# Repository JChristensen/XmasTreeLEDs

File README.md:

# Xmas Tree LEDs
https://github.com/JChristensen/XmasTreeLEDs  
README file  
Jack Christensen  
Nov-2023

## License
  
Xmas Tree LEDs by Jack Christensen is licensed under a [Creative Commons Attribution-ShareAlike 4.0 International License](http://creativecommons.org/licenses/by-sa/4.0/).

## Overview
Blinkenlights for a small ceramic Christmas Tree. Uses an ATTiny84A microcontroller and a boost regulator to maintain constant voltage to the circuit. Battery is two AAA cells and fits under the base.

See the [firmware here](https://github.com/JChristensen/XmasTree).  
PC boards can be ordered from [OSH Park](https://oshpark.com/shared_projects/T9Cb02lh).  
A bill of materials is available at [Mouser Electronics](https://www.mouser.com/ProjectManager/ProjectDetail.aspx?AccessID=e903af6094) and also in this repo.  

https://github.com/JChristensen/XmasTreeLEDs/assets/762571/b531e305-ae8b-4c04-a3d2-77f9e12bad94

https://github.com/JChristensen/XmasTreeLEDs/assets/762571/8232f8c4-e6b6-4896-a1eb-c29be3a8e65b

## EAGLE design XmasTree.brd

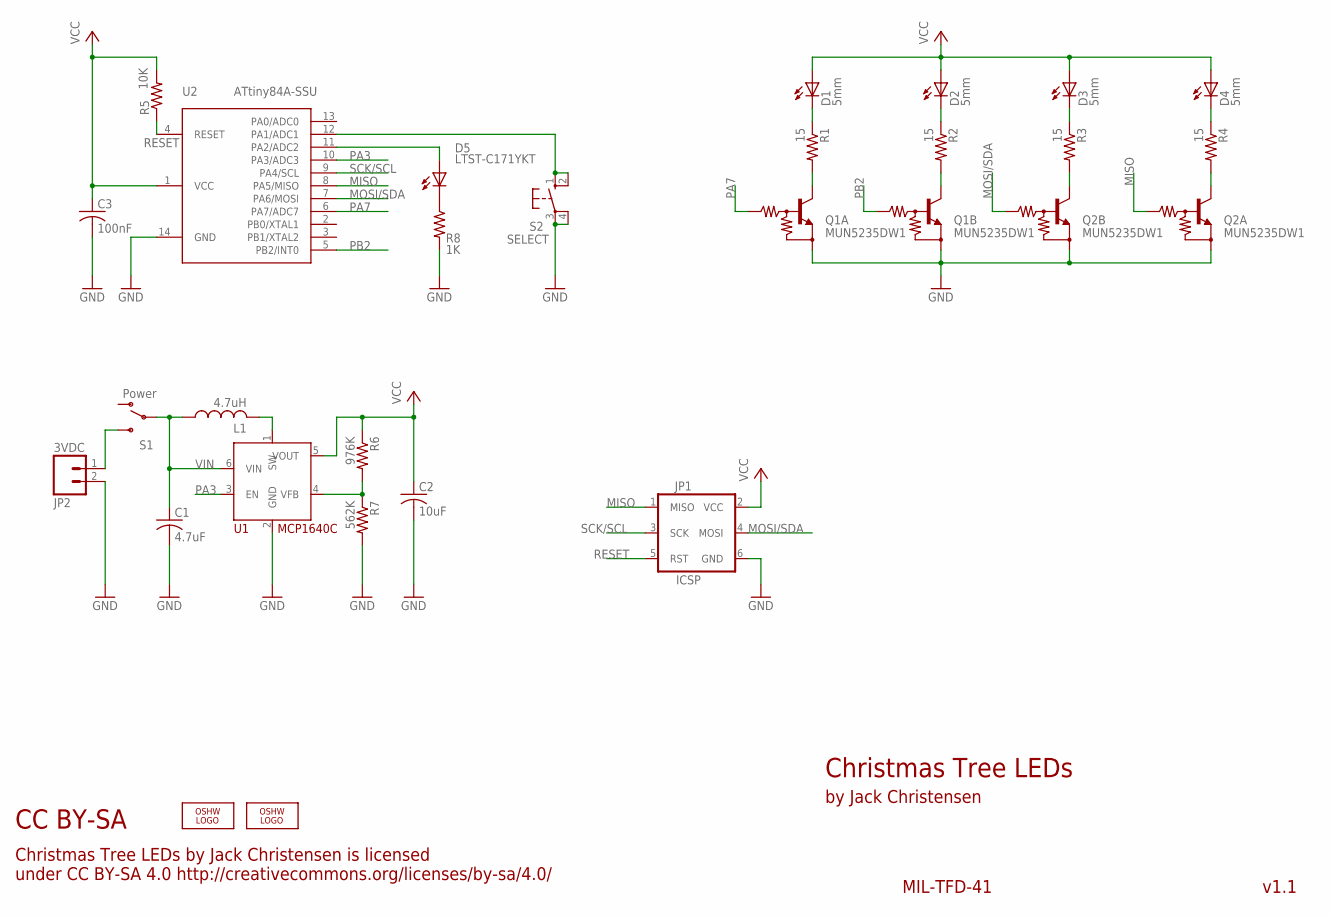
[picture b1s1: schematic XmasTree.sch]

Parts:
C1: 4.7uF; M0805
C2: 10uF; M0805
C3: 100nF; M0805
D1, D2, D3, D4: 5mm; LED5MM
D5: LTST-C171YKT; D0805
JP1: ICSP; 2X3_LOCK
JP2: 3VDC; 1X02_LONGPADS
L1: 4.7uH; C1210K
LOGO1, LOGO2: OSHW_LOGO_8MILX0150-NT; OSHW_8X150_NOTEXT
Q1, Q2: MUN5235DW1; SOT363_PHILIPS
R1, R2, R3, R4: 15; M0805
R5: 10K; M0805
R6: 976K; M0805
R7: 562K; M0805
R8: 1K; M0805
S1: Power; JS102011CQN
S2: SELECT; B3F-10XXOCT
U1: MCP1640C; SOT23-6
U2: ATtiny84A-SSU; SO14

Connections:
GND: C1.2, C2.2, C3.2, JP1.6 (GND), JP2.2, Q1.1 (E), Q1.4 (E), Q2.1 (E), Q2.4 (E), R7.2, R8.2, S2.3, S2.4 (P1), U1.2 (GND), U2.14 (GND)
MISO: JP1.1 (MISO), Q2.5 (B), U2.8 (PA5/MISO)
MOSI/SDA: JP1.4 (MOSI), Q2.2 (B), U2.7 (PA6/MOSI)
unnamed: D1.K (C), R1.1
unnamed: R6.2, R7.1, U1.4 (VFB)
unnamed: D2.K (C), R2.1
unnamed: Q2.6 (C), R3.2
unnamed: Q1.3 (C), R1.2
unnamed: JP2.1, S1.P$3 (S)
unnamed: L1.2, U1.1 (SW)
unnamed: Q1.6 (C), R2.2
unnamed: Q2.3 (C), R4.2
unnamed: D5.K (C), R8.1
unnamed: D5.A, U2.11 (PA2/ADC2)
unnamed: S2.1 (S), S2.2 (S1), U2.12 (PA1/ADC1)
unnamed: D4.K (C), R4.1
unnamed: D3.K (C), R3.1
PA3: U1.3 (EN), U2.10 (PA3/ADC3)
PA7: Q1.5 (B), U2.6 (PA7/ADC7)
PB2: Q1.2 (B), U2.5 (PB2/INT0)
RESET: JP1.5 (RST), R5.1, U2.4 (RESET)
SCK/SCL: JP1.3 (SCK), U2.9 (PA4/SCL)
VCC: C2.1, C3.1, D1.A, D2.A, D3.A, D4.A, JP1.2 (VCC), R5.2, R6.1, U1.5 (VOUT), U2.1 (VCC)
VIN: C1.1, L1.1, S1.P$2, U1.6 (VIN)

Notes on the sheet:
Christmas Tree LEDs
by Jack Christensen
Christmas Tree LEDs by Jack Christensen is licensed under CC BY-SA 4.0 http://creativecommons.org/licenses/by-sa/4.0/
CC BY-SA
v1.1
MIL-TFD-41

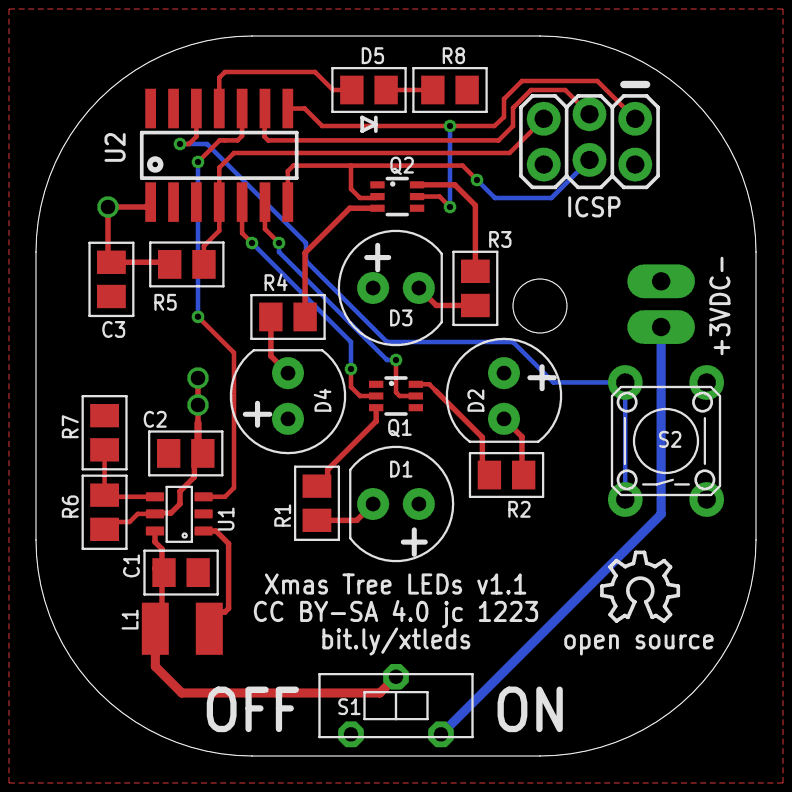
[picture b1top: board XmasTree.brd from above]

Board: 2 copper layers, 40.0 x 40.0 mm, 27 parts (1 on the bottom side), 24 nets.

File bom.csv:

Bill of Materials,,,,,
Xmas Tree LEDs,,,,,
by Jack Christensen,,,,,
Nov-2023,,,,,
https://www.mouser.com/ProjectManager/ProjectDetail.aspx?Acc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,,,,,
,,,,,
Part,Qty,Mouser #,Description,Mfr. #,Manufacturer
B1,1,534-2489,"Cylindrical Battery Contacts, Clips, Holders & Springs 2 AAA cell holder Densi-Pak",2489,Keystone Electronics
C1,1,187-CL21A475KPFNNNE,Multilayer Ceramic Capacitors MLCC - SMD/SMT 4.7uF+/-10% 10V X5R 0805,CL21A475KPFNNNE,Samsung Electro-Mechanics
C2,1,187-CL21A106KPCLQNC,Multilayer Ceramic Capacitors MLCC - SMD/SMT 10uF+/-10% 10V X5R 2 0805,CL21A106KPCLQNC,Samsung Electro-Mechanics
C3,1,581-08053C104KAT4A,Multilayer Ceramic Capacitors MLCC – SMD/SMT 25V 0.1uF X7R 0805 10%,08053C104KAT4A,KYOCERA AVX
D1-D4,4,941-C513AWSNCX0Z0342,Standard LEDs - Through Hole White,C513A-WSN-CX0Z0342,Cree LED
D5,1,859-LTST-C171YKT,Standard LEDs - SMD Yellow Clear 588nm,LTST-C171YKT,Lite-On
JP1,1,474-PRT-12807,"Header - 2x3 (Male, 0.1"")",PRT-12807,SparkFun Electronics
JP2,0,Board footprint only,Solder pads,n/a,n/a
L1,1,963-CBC3225T4R7MR,Power Inductors - SMD 1210 4.7uH 130mOhms +/-20% 1010mA HiCur,CBC3225T4R7MR,TAIYO YUDEN
Q1-Q2,2,863-MUN5235DW1T1G,Bipolar Transistors - Pre-Biased 100mA 50V BRT Dual NPN,MUN5235DW1T1G,onsemi
R1-R4,4,660-RK73H2ATTD15R0F,Thick Film Resistors - SMD 1/4W 15 OHM 1%, RK73H2ATTD15R0F,KOA Speer
R5,1,660-RK73H1JTTDD1002F,Thick Film Resistors - SMD 1/10watts 10Kohms 1%,RK73H1JTTDD1002F,KOA Speer
R6,1,660-RK73H1ETTP9763F,Thick Film Resistors - SMD 0.1watt 976Kohms 1%,RK73H1ETTP9763F,KOA Speer
R7,1,660-RK73H2ATTD5623F,Thick Film Resistors - SMD 1/4W 562K OHM 1%,RK73H2ATTD5623F,KOA Speer
R8,1,660-RK73H1JTTDD1001F,Thick Film Resistors - SMD 1/8watts 1Kohms 1%,RK73H1JTTDD1001F,KOA Speer
S1,1,611-JS102011CQN,Slide Switches Sub-Miniature Slide Switch,JS102011CQN,C&K Switches
S2,1,653-B3F-1020,Tactile Switches 6X6 Flat 5mm Btn Force 100g w/o Grd,B3F-1020,Omron
U1,1,579-MCP1640CT-I/CHY,Switching Voltage Regulators 500 kHz 300 mA Syn Boost Converter,MCP1640CT-I/CHY,Microchip
U2,1,556-ATTINY84A-SSU,8-bit Microcontrollers - MCU 20MHz Ind. Grade,ATTINY84A-SSU,Microchip

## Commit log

2023-11-28 Initial commit.
2023-11-28 Add select button.
2023-11-28 Add BOMs.
2023-12-05 Update LED dropping resistor values.
2023-12-09 Board tweaks.
2023-12-09 Add images.
2023-12-09 Add videos.
2023-12-09 Try .mov video format.
2023-12-09 Add video links to README file.
2023-12-21 Cosmetic tweaks to schematic.
2023-12-21 Update schematic image file.

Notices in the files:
XmasTree.brd:
CC BY-SA 4.0 jc 1223
parts and their libraries:
SparkFun: Licensing: CC v3.0 Share-Alike You are welcome to use this library for commercial purposes.
